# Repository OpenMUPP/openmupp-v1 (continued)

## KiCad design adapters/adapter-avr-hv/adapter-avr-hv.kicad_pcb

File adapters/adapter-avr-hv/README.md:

# adapter-avr-hv

This adapter programs AVR parts that need a high voltage (12 V) on one pin. This is necessary when a fuse disables the normal programming interface. Examples are the RSTDISBL fuse and the RSTPINCFG fuse. The adapter has slot 8 (R1 = 39 kΩ).

The probe supplies all levels on J1 pin 19: 0 V, `VTREF` and VPP. See [Pin 19 states](../../docs/hardware.md#pin-19-states). The circuit details are in [adapters/README.md](../README.md).

## Connectors

| Ref | Type | Interface | Target parts | 12 V goes to |
|-----|------|-----------|--------------|--------------|
| J1 | 2 × 10 socket | Probe J4 | — | — |
| J2 | DIP-8 socket | HVSP | ATtiny13, ATtiny25/45/85 | Pin 1 (RESET) |
| J3 | DIP-14 socket | HVSP | ATtiny24/44/84 | Pin 4 (RESET) |
| J4 | 2 × 3 header | TPI and UPDI | ATtiny4/5/9/10, tinyAVR 0, 1 and 2 series, AVR DD | Pin 5 (RESET). With JP1 closed, also pin 1 (UPDI). |
| J5 | 1 × 4 header | Debug UART | Any | — |
| JP1 | 2-pin jumper header | HV select for J4 | — | — |

HVSP is high-voltage serial programming. TPI is the Tiny Programming Interface. UPDI is the Unified Program and Debug Interface.

Connect only one target at a time. VPP goes to J2, J3 and J4 at the same time.

### J2 and J3: HVSP sockets

Put the part directly into the socket. The probe supplies `VCC` from `VTREF`.

| HVSP signal | J1 pin | J2 (DIP-8) | J3 (DIP-14) |
|-------------|--------|------------|-------------|
| RESET (12 V) | 19 | 1 (PB5) | 4 (PB3) |
| SCI (clock) | 6 | 2 (PB3) | 2 (PB0) |
| SDI (data in) | 10 | 5 (PB0) | 7 (PA6) |
| SII (instruction in) | 17 | 6 (PB1) | 8 (PA5) |
| SDO (data out) | 8 | 7 (PB2) | 9 (PA4) |
| `VCC` | 1 | 8 | 1 |
| GND | 3, 5, 7, 9, 20 | 4 | 14 |

HVSP entry needs three Prog_enable pins at 0 while `VCC` comes up. On J2, these pins are SDI, SII and SDO. The probe drives SDI and SII low, and R4 holds SDO low. On J3, these pins are PA0, PA1 and PA2 (pins 13, 12 and 11). R7, R6 and R5 hold them low. The pin data is from the ATtiny25/45/85 data sheet (table 20-13) and the ATtiny24A/44A/84A data sheet (table 19-13).

### J4: TPI and UPDI header

J4 uses the Microchip 6-pin layout for TPI and UPDI (Atmel-ICE user guide, tables 3-4 and 3-7).

| Pin | Function | Net | J1 pin |
|-----|----------|-----|--------|
| 1 | TPI data or UPDI | `UPDI_HV` | 12, through Q2 |
| 2 | `VTREF` | `VTREF` | 1 |
| 3 | TPI clock | `SCI_TPICLK` | 6 |
| 4 | — | Open | — |
| 5 | RESET | `RESET_VPP` | 19 |
| 6 | GND | GND | GND |

TPI data and UPDI use the same pin, J1 pin 12. The probe drives this pin open drain, with a 10 kΩ pull-up. The target pulls `UPDI_HV` high with its internal pull-up. See [UPDI on J4 pin 12](../README.md#updi-on-j4-pin-12).

### JP1: HV select

JP1 selects the J4 pin that gets 12 V. Set JP1 before you connect the target.

| JP1 | 12 V on | Use for |
|-----|---------|---------|
| Open | Pin 5 only | TPI (ATtiny4/5/9/10). UPDI parts with a separate RESET pin, for example AVR DD. |
| Closed | Pin 1 (through D1) and pin 5 | tinyAVR 0, 1 and 2 series. UPDI and RESET are on the same pin. |

**CAUTION:** Do not close JP1 for a TPI part or an AVR DD part. Pin 1 then gets 12 V, and this can damage the part.

- TPI needs 12 V on RESET only when the RSTDISBL fuse is programmed.
- The AVR DD setting is not verified against a part. Read the data sheet of the part before you use it.
- With JP1 closed, pin 5 also gets VPP. Some tinyAVR target boards connect pin 5 to the UPDI pin. Check the target board before you use it.
- The firmware can read the JP1 position before it sets VPP on. See [UPDI high-voltage pulse](../README.md#updi-high-voltage-pulse).

### J5: debug UART

| Pin | Signal | J1 pin |
|-----|--------|--------|
| 1 | GND | GND |
| 2 | RX (probe input) | 14 |
| 3 | TX (probe output) | 13 |
| 4 | `VTREF` | 1 |

All adapters have this header (see [Rules for all adapters](../README.md#rules-for-all-adapters)).

## Other parts

| Ref | Value | Function |
|-----|-------|----------|
| R1 | 39 kΩ | Adapter ID, slot 8 |
| D1 | BAT54A | With JP1 closed, connects `RESET_VPP` to `UPDI_HV` (J4 pin 1). It blocks while pin 19 is at 0 V. |
| Q2 | FDV301N | Pass switch between `UPDI_HV` and `UPDI`. It blocks 12 V from J1 pin 12. |
| R4 | 10 kΩ | Holds SDO (J2 pin 7) low at HVSP entry |
| R5, R6, R7 | 10 kΩ | Hold PA0, PA1 and PA2 on J3 low at HVSP entry |

J1 pins 2, 4, 11, 15 and 18 are not used.

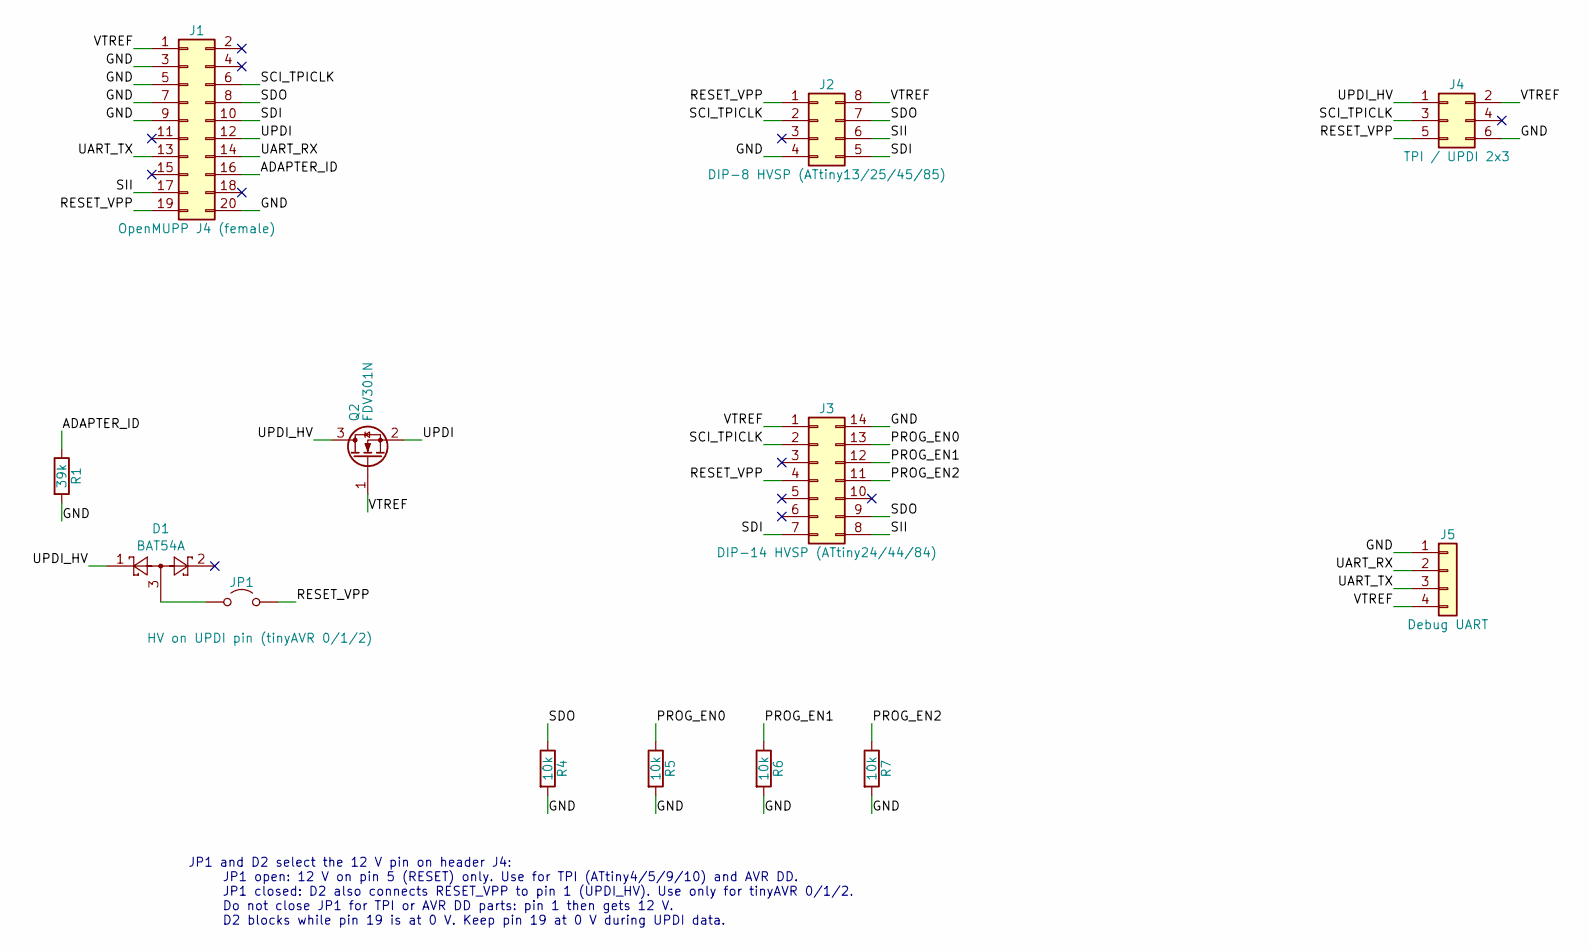
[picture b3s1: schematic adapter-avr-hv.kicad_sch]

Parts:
D1: BAT54A; SOT-23
J1: OpenMUPP J4 (female); PinSocket_2x10_P2.54mm_Horizontal
J2: DIP-8 HVSP (ATtiny13/25/45/85); DIP-8_W7.62mm_Socket
J3: DIP-14 HVSP (ATtiny24/44/84); DIP-14_W7.62mm_Socket
J4: TPI / UPDI 2x3; PinHeader_2x03_P2.54mm_Vertical
J5: Debug UART; PinHeader_1x04_P2.54mm_Vertical
JP1: HV on UPDI pin (tinyAVR 0/1/2); PinHeader_1x02_P2.54mm_Vertical
Q2: FDV301N; SOT-23
R1: 39k; R_0603
R4, R5, R6, R7: 10k; R_0603

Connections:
/ADAPTER_ID: J1.16, R1.1
/GND: J1.3, J1.5, J1.7, J1.9, J1.20, J2.4, J3.14, J4.6, J5.1, R1.2, R4.2, R5.2, R6.2, R7.2
/PROG_EN0: J3.13, R5.1
/PROG_EN1: J3.12, R6.1
/PROG_EN2: J3.11, R7.1
/RESET_VPP: J1.19, J2.1, J3.4, J4.5, JP1.2 (B)
/SCI_TPICLK: J1.6, J2.2, J3.2, J4.3
/SDI: J1.10, J2.5, J3.7
/SDO: J1.8, J2.7, J3.9, R4.1
/SII: J1.17, J2.6, J3.8
/UART_RX: J1.14, J5.2
/UART_TX: J1.13, J5.3
/UPDI: J1.12, Q2.2 (S)
/UPDI_HV: D1.1, J4.1, Q2.3 (D)
/VTREF: J1.1, J2.8, J3.1, J4.2, J5.4, Q2.1 (G)
unnamed: D1.3, JP1.1 (A)

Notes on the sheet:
JP1 and D2 select the 12 V pin on header J4: JP1 open: 12 V on pin 5 (RESET) only. Use for TPI (ATtiny4/5/9/10) and AVR DD. JP1 closed: D2 also connects RESET_VPP to pin 1 (UPDI_HV). Use only for tinyAVR 0/1/2. Do not close JP1 for TPI or AVR DD parts: pin 1 then gets 12 V. D2 blocks while pin 19 i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

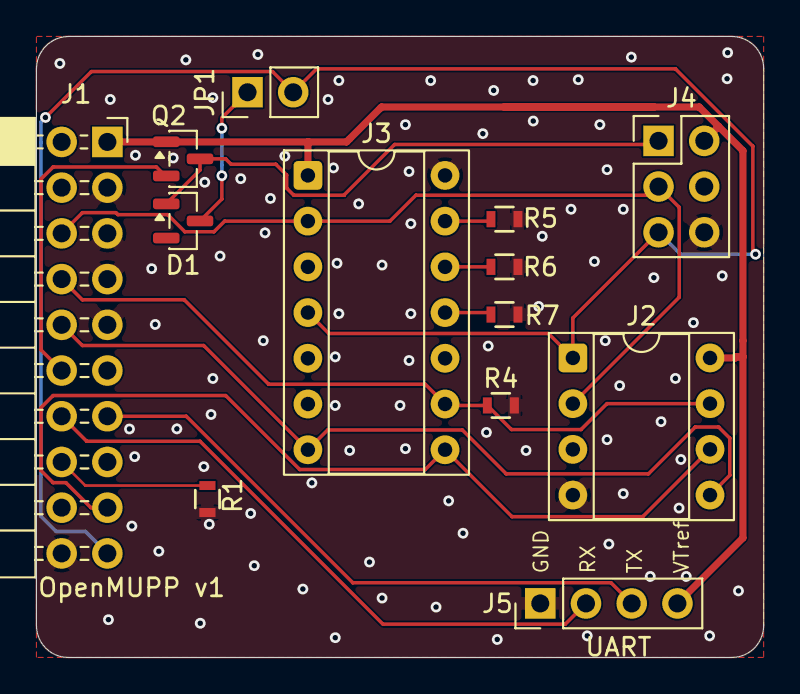
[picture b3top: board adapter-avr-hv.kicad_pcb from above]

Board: 2 copper layers, 40.4 x 34.5 mm, 13 parts (0 on the bottom side), 16 nets.

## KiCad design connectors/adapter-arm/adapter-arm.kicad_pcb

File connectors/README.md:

# Target adapters for OpenMUPP v1

Each folder is a KiCad 10 project with the schematic of one target adapter. The projects have no board layout yet.

| Folder                                     | Adapter          | Slot | R<sub>ID</sub> | Target connectors                                              |
|--------------------------------------------|------------------|------|----------------|----------------------------------------------------------------|
| [adapter-avr-jtag-isp](adapter-avr-jtag-isp/) | AVR variant A | 1 | 1.1 kΩ | Atmel-ICE 10 (1.27 mm), AVR JTAG 10 (2.54 mm), 2 × 3 ISP |
| [adapter-arm](adapter-arm/)                | Arm              | 4    | 6.8 kΩ         | ARM JTAG 20, Cortex Debug 10, STDC14                           |
| [adapter-pin-header](adapter-pin-header/)  | Pin header       | 5    | 10 kΩ          | 1 × 6 SWD / CH32 / SWIM, 1 × 4 ST SWIM, 2 × 5 WCH-LinkE layout |
| [adapter-avr-hv](adapter-avr-hv/)          | AVR high voltage | 8    | 39 kΩ          | DIP-8 and DIP-14 sockets (HVSP), 2 × 3 TPI and UPDI            |
| [adapter-pic-hv](adapter-pic-hv/)          | PIC high voltage | 9    | 91 kΩ          | PICkit ICSP 1 × 6                                              |

The slot table and the J4 pinout are in the [main README](../README.md#adapter-boards-and-adapter-id).

## Rules for all adapters

1. J1 is a female 2 × 10 header, 2.54 mm. It plugs directly onto J4 of the probe. The pin numbers of J1 are the J4 pin numbers.
2. One 1 % resistor (R1) goes from J1 pin 16 to GND. J1 pin 16 never goes to the target.
3. J1 pin 2 (reserved) stays open. J1 pin 19 (VPP) stays open on each adapter that is not a high-voltage adapter.
4. Each adapter has a 1 × 4 debug UART header: 1 GND, 2 RX (probe input), 3 TX (probe output), 4 `VTREF`. The labels are from the probe side. Pins 1 to 3 have the same order as J2 on the main board. Pin 4 lets the UART work without a debug connector to the target.
5. Connect only one target connector at a time.

## Female header on J4

J4 on the probe is a shrouded, right-angle header (`IDC-Header_2x10_P2.54mm_Horizontal`). The adapter schematics use `PinSocket_2x10_P2.54mm_Horizontal` for J1, so the adapter board is in the same plane as the probe. Before layout, check these items:

- **Fit.** The socket body must go into the shroud of J4. Measure the shroud opening and the socket body.
- **Pin mirror.** The socket and the header mate face to face. Make sure that J1 pin 1 touches J4 pin 1 in the layout.
- **Polarity.** A plain socket has no key, so it can go in rotated by 180°. Then J1 pin 16 touches a probe GND pin, and the probe pin 16 touches an adapter GND pin. The adapter ID reads 0 Ω (the fault slot). The firmware must then keep the shifter outputs, the target power and VPP off. Use a keyed socket, or add a mechanical key on the adapter board, if possible.

## RESET and MCLR on J4 pin 19

`adapter-avr-hv` and `adapter-pic-hv` connect the target RESET or MCLR pin directly to J1 pin 19. The nets are `RESET_VPP` and `MCLR_VPP`. The probe gives pin 19 three levels: 0 V (reset), `VTREF` (run) and VPP (program). See [Pin 19 states](../docs/hardware.md#pin-19-states). Thus the adapters have no reset circuit, and J1 pin 18 (`AUX2`) is not used.

HVSP entry needs RESET at 0 V while `VCC` comes up. Then RESET must go to 12 V after a short time. Q6 on the probe holds pin 19 at 0 V. The firmware can set `VPP_ON` before `VCC` comes up, because Q6 holds pin 19 low against the current limit. Then the firmware releases Q6 at the time that the data sheet gives. Pin 19 then goes to VPP in some µs.

## UPDI on J4 pin 12

UPDI uses J4 pin 12 (nRESET / debugWIRE), not J4 pin 4 (SWDIO). The reasons:

- The UPDI pin of a tinyAVR is a weak driver. The ATtiny1614/16/17 data sheet (DS40002204A, table 36-16, VOL2) guarantees only 0.1 mA at 1.8 V and 0.5 mA at 5 V.
- J4 pin 4 has a 2.2 kΩ pull-up on the probe. The target must then sink 0.8 mA to 2.3 mA. See issue [#6](https://github.com/OpenMUPP/openmupp-v1/issues/6).
- J4 pin 12 has a 10 kΩ pull-up. The target must sink 0.18 mA at 1.8 V and 0.5 mA at 5 V.
- J4 pin 12 is open-drain (Q1 on the probe). This is the physical layer that UPDI expects.

Effects on the firmware:

- The read-back of J4 pin 12 goes to PB11 (USART3_RX). The USART receives UPDI and sees its own transmit.
- The CH32V307 USART cannot invert TX, so the firmware sends UPDI in software through Q1 (PB12). debugWIRE uses the same method.
- The rise time with 10 kΩ and about 30 pF to 50 pF is about 0.3 µs to 0.5 µs. This is sufficient for 225 kbps (the maximum UPDI rate at 1.8 V). It is not sufficient for 0.9 Mbps. These values are estimates, not measurements.
- The debug UART (J4 pins 13 and 14) stays free during UPDI.

On `adapter-avr-hv`, TPI data also uses J4 pin 12, through the same path as UPDI. The TPIDATA pin of the ATtiny4/5/9/10 has an internal pull-up in TPI mode (20 kΩ to 50 kΩ). The target drives a 0 and the first 1 of a sequence. Then the pull-up holds the line high (ATtiny4/5/9/10 data sheet DS40002060A, section 15.3.8). Thus TPI and UPDI see the same physical layer: open drain with a pull-up. Other TPI adapters can still use J4 pin 4.

## UPDI high-voltage pulse

`adapter-avr-hv` has one 2 × 3 header (J4) for TPI and UPDI. JP1, a 2-pin jumper header, selects the pin that gets the high voltage (HV):

| JP1 | Use | Pin 1 (data) | Pin 5 | HV goes to |
|-----|-----|--------------|-------|------------|
| Open | TPI (ATtiny4/5/9/10). UPDI with a separate RESET pin, for example AVR DD. | `UPDI_HV` (through Q2 to J1 pin 12) | `RESET_VPP` (J1 pin 19) | Pin 5 |
| Closed | UPDI with HV on the UPDI pin (tinyAVR 0, 1 and 2 series) | `UPDI_HV` (through Q2 to J1 pin 12) | `RESET_VPP` (J1 pin 19) | Pin 1 and pin 5 |

On the tinyAVR 0, 1 and 2 series, the UPDI pin and the RESET pin are the same pin. The data sheet calls the HV entry "UPDI Enable with High-Voltage Override of RESET Pin". The HV detection level (V<sub>HVRST</sub>) is 11.5 V to 12.5 V. The AVR DD setting is not verified against a part. Check the data sheet of each part before you use it.

The TPIDATA pin and the AVR DD UPDI pin must not get 12 V. Thus JP1 must be open for these parts. With JP1 closed, pin 5 also gets VPP. On a tinyAVR target board, pin 5 is usually not connected, so this is permitted. Some target boards connect pin 5 to the UPDI pin. Then pin 19 at 0 V holds the UPDI line low. Check the target board before you use it.

The parts of the UPDI path:

1. D2 (BAT54W) and JP1 connect J1 pin 19 to `UPDI_HV` when JP1 is closed. D2 has a drop of about 0.3 V. Set VPP to about 12.3 V for 12 V on the UPDI pin. `RESET_VPP` has no diode, so it gets VPP directly.
2. Q2 (FDV301N) is a pass switch between `UPDI_HV` (drain) and `UPDI` (source, J1 pin 12). The gate is on `VTREF`. When `UPDI_HV` is at 12 V, Q2 is off and the 10 kΩ pull-up on the probe holds `UPDI` at `VTREF`. The body diode is then reverse biased. The ESD diode on J4 pin 12 of the probe clamps at about 6 V, so this protection is necessary.
3. While VPP is off, Q2 passes UPDI and TPI data in both directions. The probe pulls `UPDI` high (10 kΩ). The internal pull-up of the target pulls `UPDI_HV` high. The adapter has no pull-up on `UPDI_HV`, so it adds no load to the weak UPDI pad.
4. With JP1 closed, keep pin 19 at 0 V (`VPP_PD` high) during UPDI, except during the HV pulse. In the run state, pin 19 is at `VTREF`. Then R39 on the probe and D2 pull `UPDI_HV` up. When the target sends a 0, it must also sink this current: about 0.13 mA at 1.8 V and 0.45 mA at 5 V. The UPDI pad guarantees only 0.1 mA at 1.8 V. At 0 V on pin 19, D2 blocks and adds no load.
5. The firmware can read the JP1 position before it sets VPP on. Put pin 19 in the run state and set Q1 on. With JP1 closed, current flows from R39 through D2, Q2 and Q1. `VPP_SENSE2` then reads less than about 0.5 V. With JP1 open, `VPP_SENSE2` reads the run level. If the JP1 position does not agree with the selected target, the firmware must not set VPP on. This value is an estimate, not a measurement.

Limits:

- Q2 passes a low level only when `VTREF` is above V<sub>GS(th)</sub>. The FDV301N has 1.06 V maximum, so `VTREF` of 1.8 V is sufficient. The tinyAVR parts run from 1.8 V to 5.5 V.
- The gate-source voltage of the FDV301N must stay above −0.3 V. The source (`UPDI`) has a 10 kΩ pull-up to the gate potential (`VTREF`), so it does not go above the gate. Q2 leakage (I<sub>DSS</sub> 1 µA maximum at 20 V) moves `UPDI` by about 10 mV.
- A low-to-high edge on `UPDI_HV` above `VTREF` − V<sub>GS(th)</sub> comes from the target pull-up only. This is slower than on `UPDI`. Check the rise time at the UPDI baud rate and at the TPI clock rate.
- VPP goes to `RESET_VPP`. With JP1 closed, it also goes to `UPDI_HV` at the same time. Connect only one target to J2, J3 or J4.
- After the pulse, the line must return to the normal level quickly: the debugger drives it low 1 µs to 10 µs after the HV ends (data sheet figure 33-6). D2 cannot pull `UPDI_HV` down. The probe pulls J4 pin 12 low through its Q1. The adapter Q2 then conducts, because its gate is at `VTREF`, and pulls `UPDI_HV` low. At the same time, Q6 on the probe pulls pin 19 to 0 V in less than 1 µs, so D2 blocks at once.
- The TPS2553 on the probe has a soft start of some milliseconds. Check the pulse timing in the target data sheet.

## HVSP pull-downs

HVSP entry needs the three Prog_enable pins at 0 while `VCC` comes up. R4 to R7 (10 kΩ) hold them low on `adapter-avr-hv`. These resistors are not in the adapter plan. The pins come from the ATtiny datasheets:

| Part              | Prog_enable[0..2]           | Resistors                                          |
|-------------------|-----------------------------|----------------------------------------------------|
| ATtiny13/25/45/85 | SDI, SII, SDO (PB0 to PB2)  | The probe drives SDI and SII low. R4 holds SDO low |
| ATtiny24A/44A/84A | PA0, PA1, PA2 (pins 13, 12, 11) | R5, R6, R7                                     |

J4 pin 8 (SDO input) is an input only, so the probe cannot hold SDO low. The target drives SDO against R4 after entry.

## Items to check before layout

- **WCH-LinkE layout.** The positions of GND, 3V3 and 5V on the WCH-LinkE header come from the schematic text only. Check them on a real WCH-LinkE. Pin 8 (3V3) connects to `VTREF`. Pin 10 (5V) stays open.
- **ST SWIM order.** Check the order (VDD, SWIM, GND, NRST) against ST UM1075.
- **1.27 mm headers.** Cortex Debug 10 and STDC14 use plain 1.27 mm pin headers in the schematic. Use shrouded, keyed parts (Samtec FTSH-105 and FTSH-107, or equal). Put their footprints in the `kicad-footprints` repository.
- **Atmel-ICE 10.** J2 on `adapter-avr-jtag-isp` is a plain 1.27 mm pin header in the schematic. Use a shrouded, keyed part, as for Cortex Debug 10. J4 (AVR JTAG 10, 2.54 mm) uses a shrouded IDC header.
- **Footprint libraries.** All resistors are 0603 and use `resistors:R_0603` from the `kicad-footprints` repository, as on the main board.

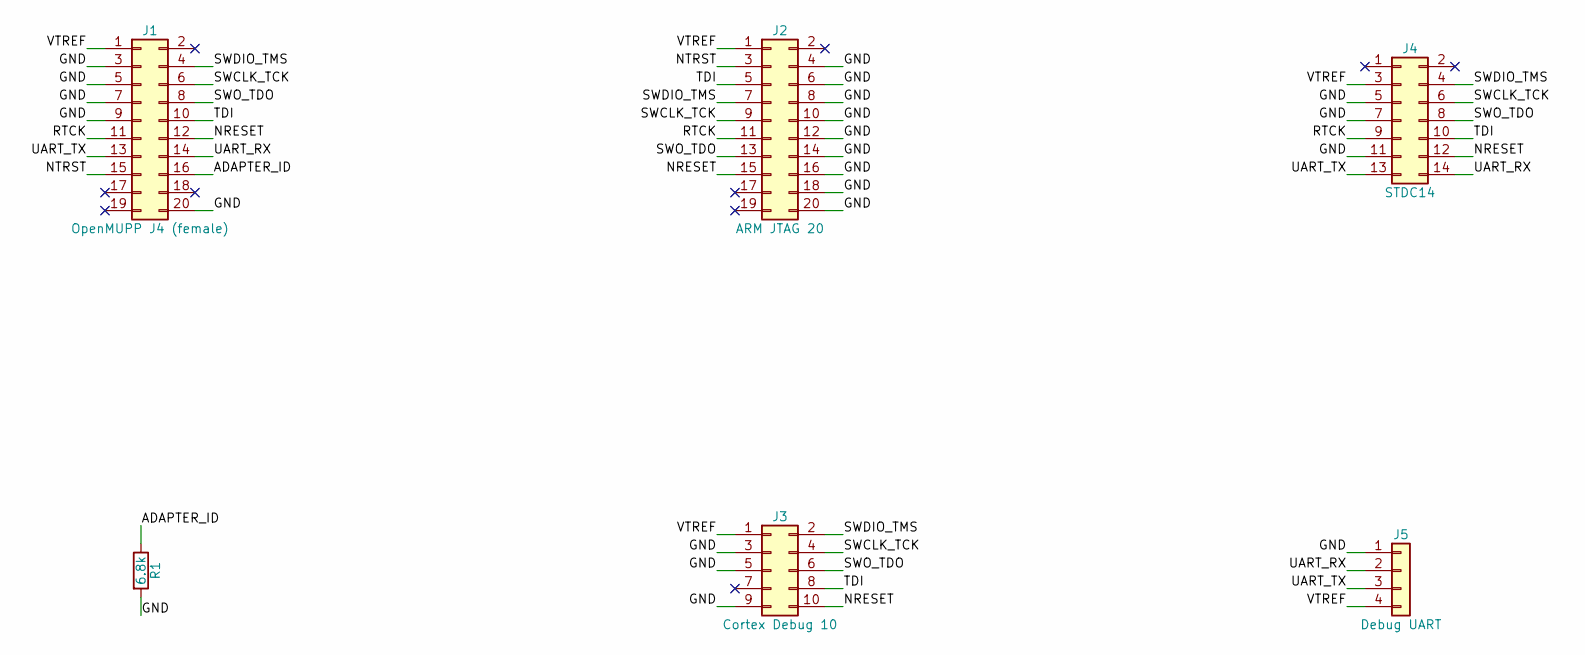
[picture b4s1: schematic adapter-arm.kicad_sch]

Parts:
J1: OpenMUPP J4 (female); PinSocket_2x10_P2.54mm_Horizontal
J2: ARM JTAG 20; IDC-Header_2x10_P2.54mm_Vertical
J3: Cortex Debug 10; PinHeader_2x05_P1.27mm_Vertical_SMD
J4: STDC14; PinHeader_2x07_P1.27mm_Vertical_SMD
J5: Debug UART; PinHeader_1x04_P2.54mm_Vertical
R1: 6.8k; R_0603

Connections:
/ADAPTER_ID: J1.16, R1.1
/GND: J1.3, J1.5, J1.7, J1.9, J1.20, J2.4, J2.6, J2.8, J2.10, J2.12, J2.14, J2.16, J2.18, J2.20, J3.3, J3.5, J3.9, J4.5, J4.7, J4.11, J5.1, R1.2
/NRESET: J1.12, J2.15, J3.10, J4.12
/NTRST: J1.15, J2.3
/RTCK: J1.11, J2.11, J4.9
/SWCLK_TCK: J1.6, J2.9, J3.4, J4.6
/SWDIO_TMS: J1.4, J2.7, J3.2, J4.4
/SWO_TDO: J1.8, J2.13, J3.6, J4.8
/TDI: J1.10, J2.5, J3.8, J4.10
/UART_RX: J1.14, J4.14, J5.2
/UART_TX: J1.13, J4.13, J5.3
/VTREF: J1.1, J2.1, J3.1, J4.3, J5.4

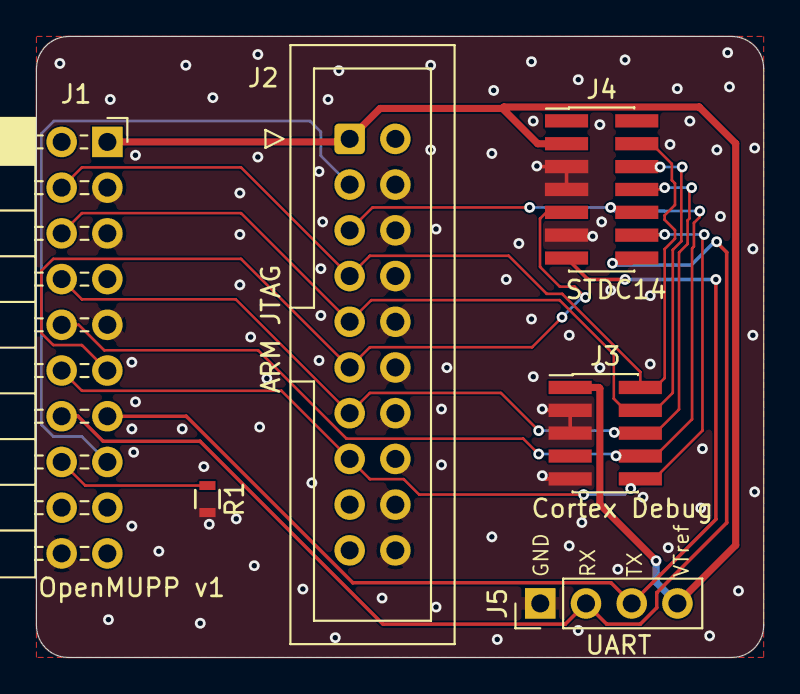
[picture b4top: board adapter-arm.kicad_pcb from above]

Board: 2 copper layers, 40.4 x 34.5 mm, 6 parts (0 on the bottom side), 12 nets.

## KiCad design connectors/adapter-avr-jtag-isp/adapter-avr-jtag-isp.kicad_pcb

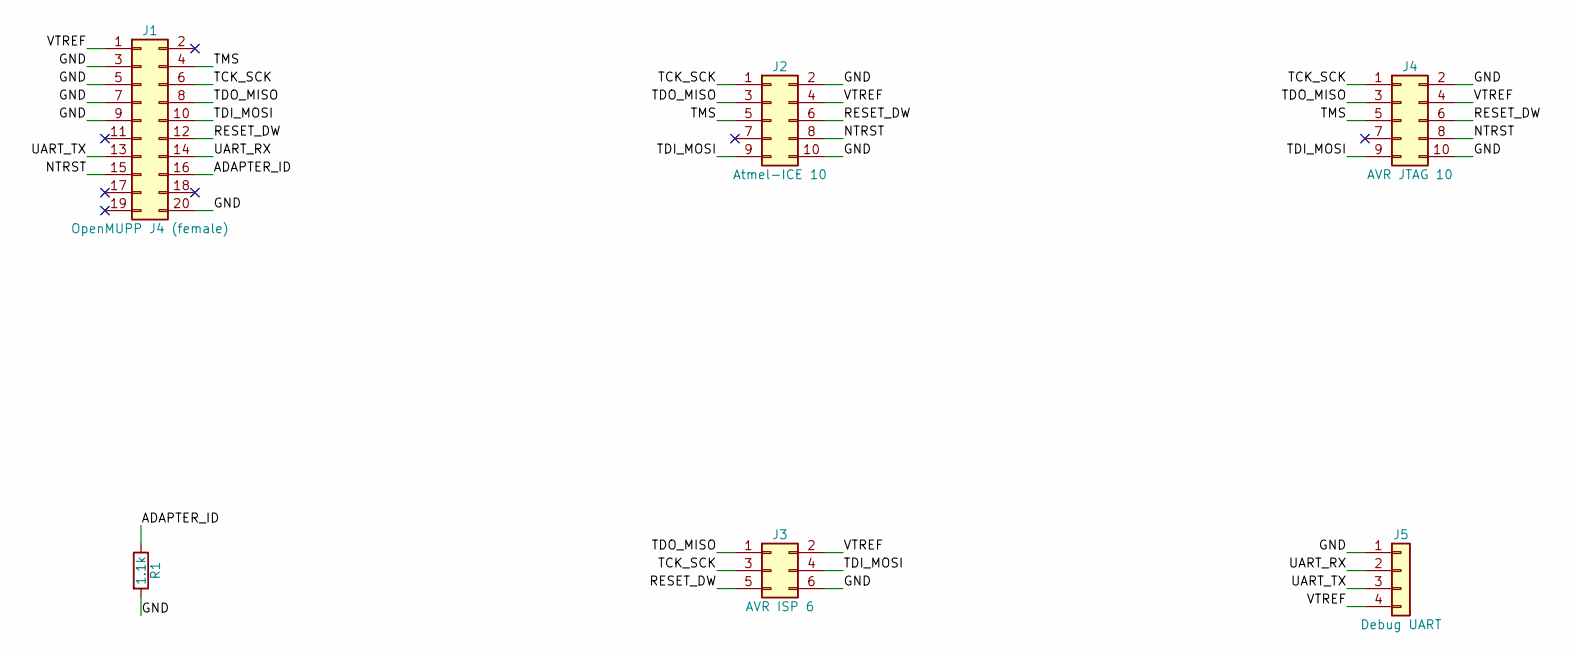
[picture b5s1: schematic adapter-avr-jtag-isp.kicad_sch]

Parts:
J1: OpenMUPP J4 (female); PinSocket_2x10_P2.54mm_Horizontal
J2: Atmel-ICE 10; PinHeader_2x05_P1.27mm_Vertical_SMD
J3: AVR ISP 6; PinHeader_2x03_P2.54mm_Vertical
J4: AVR JTAG 10; IDC-Header_2x05_P2.54mm_Vertical
J5: Debug UART; PinHeader_1x04_P2.54mm_Vertical
R1: 1.1k; R_0603

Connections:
/ADAPTER_ID: J1.16, R1.1
/GND: J1.3, J1.5, J1.7, J1.9, J1.20, J2.2, J2.10, J3.6, J4.2, J4.10, J5.1, R1.2
/NTRST: J1.15, J2.8, J4.8
/RESET_DW: J1.12, J2.6, J3.5, J4.6
/TCK_SCK: J1.6, J2.1, J3.3, J4.1
/TDI_MOSI: J1.10, J2.9, J3.4, J4.9
/TDO_MISO: J1.8, J2.3, J3.1, J4.3
/TMS: J1.4, J2.5, J4.5
/UART_RX: J1.14, J5.2
/UART_TX: J1.13, J5.3
/VTREF: J1.1, J2.4, J3.2, J4.4, J5.4

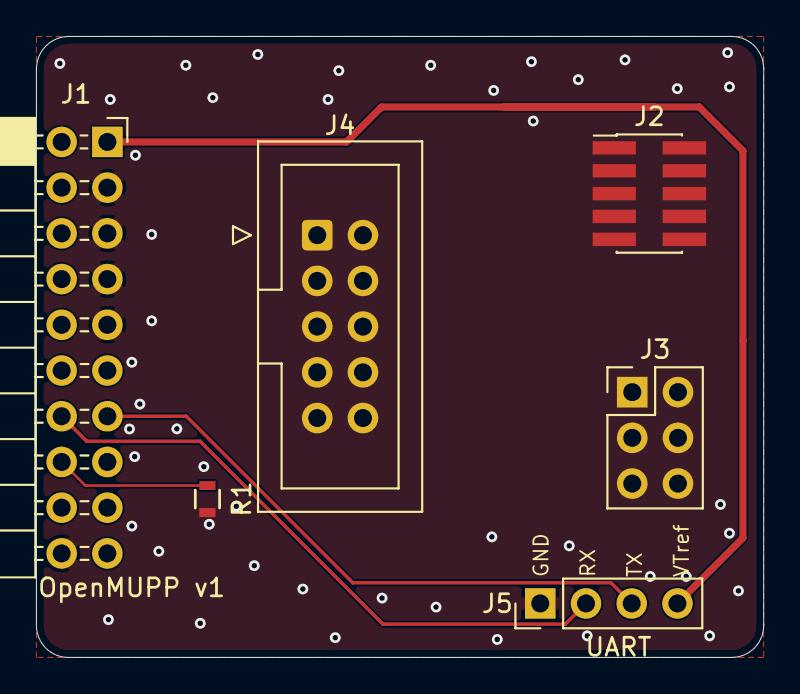
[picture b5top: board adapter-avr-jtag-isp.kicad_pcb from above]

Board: 2 copper layers, 40.4 x 34.5 mm, 6 parts (0 on the bottom side), 11 nets.

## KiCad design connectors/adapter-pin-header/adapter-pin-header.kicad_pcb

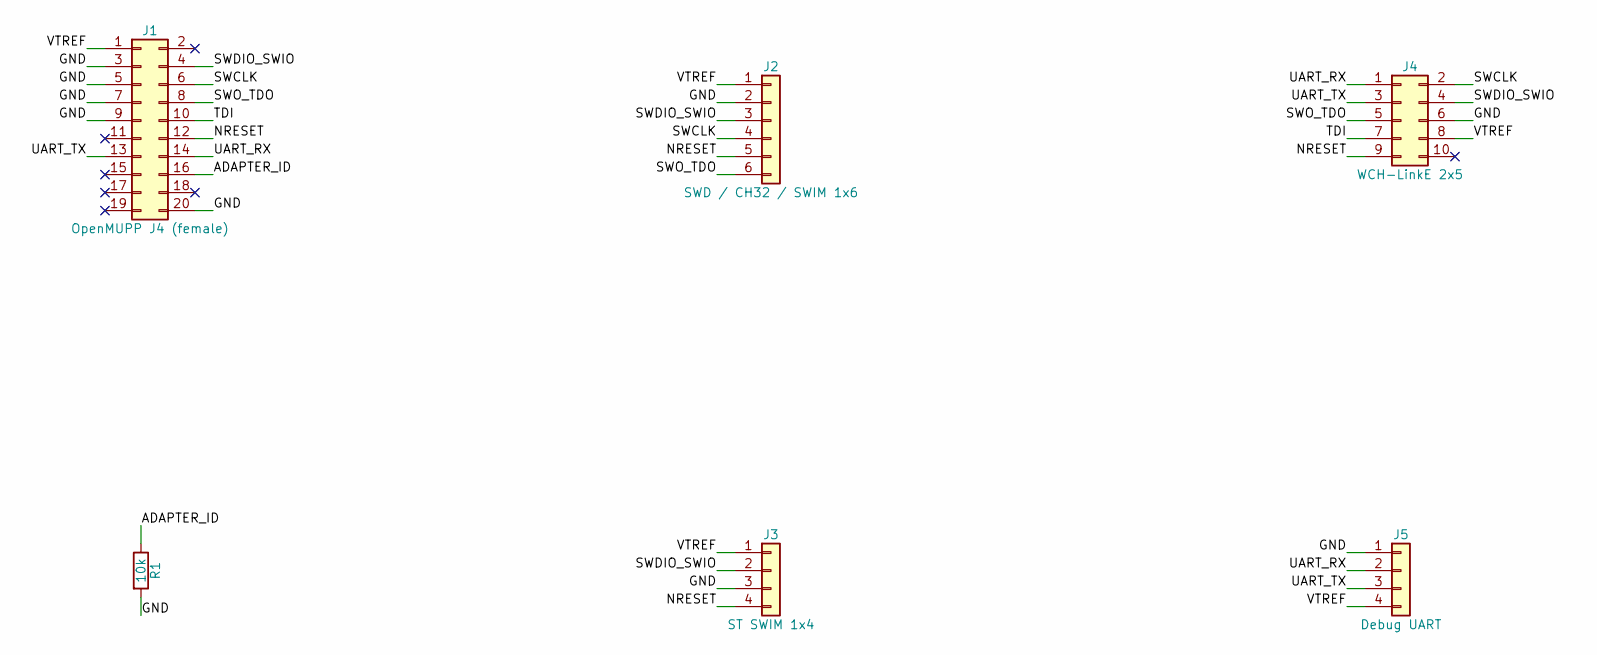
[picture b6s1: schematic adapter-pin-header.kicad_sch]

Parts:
J1: OpenMUPP J4 (female); PinSocket_2x10_P2.54mm_Horizontal
J2: SWD / CH32 / SWIM 1x6; PinHeader_1x06_P2.54mm_Vertical
J3: ST SWIM 1x4; PinHeader_1x04_P2.54mm_Vertical
J4: WCH-LinkE 2x5; PinHeader_2x05_P2.54mm_Vertical
J5: Debug UART; PinHeader_1x04_P2.54mm_Vertical
R1: 10k; R_0603

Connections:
/ADAPTER_ID: J1.16, R1.1
/GND: J1.3, J1.5, J1.7, J1.9, J1.20, J2.2, J3.3, J4.6, J5.1, R1.2
/NRESET: J1.12, J2.5, J3.4, J4.9
/SWCLK: J1.6, J2.4, J4.2
/SWDIO_SWIO: J1.4, J2.3, J3.2, J4.4
/SWO_TDO: J1.8, J2.6, J4.5
/TDI: J1.10, J4.7
/UART_RX: J1.14, J4.1, J5.2
/UART_TX: J1.13, J4.3, J5.3
/VTREF: J1.1, J2.1, J3.1, J4.8, J5.4

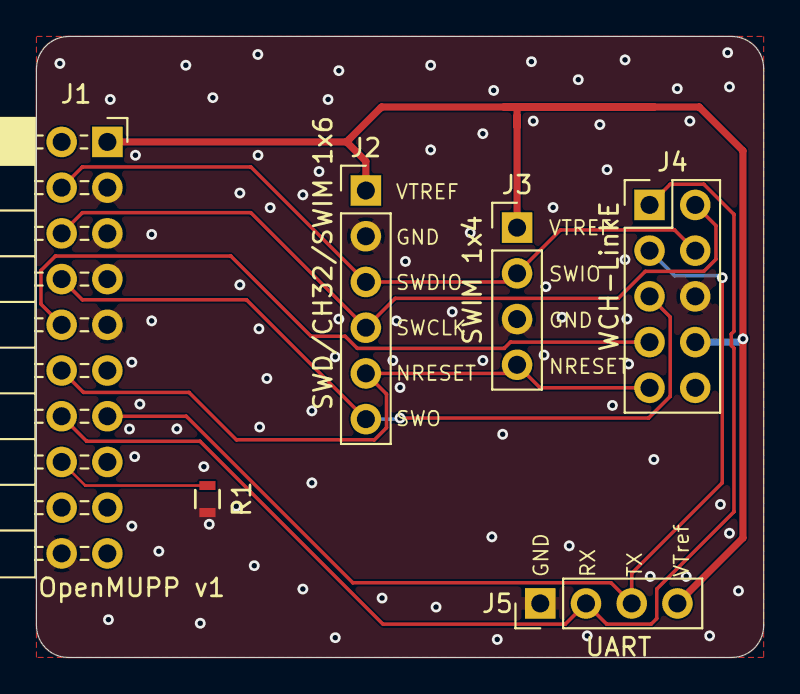
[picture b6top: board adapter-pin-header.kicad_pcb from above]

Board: 2 copper layers, 40.4 x 34.5 mm, 6 parts (0 on the bottom side), 10 nets.

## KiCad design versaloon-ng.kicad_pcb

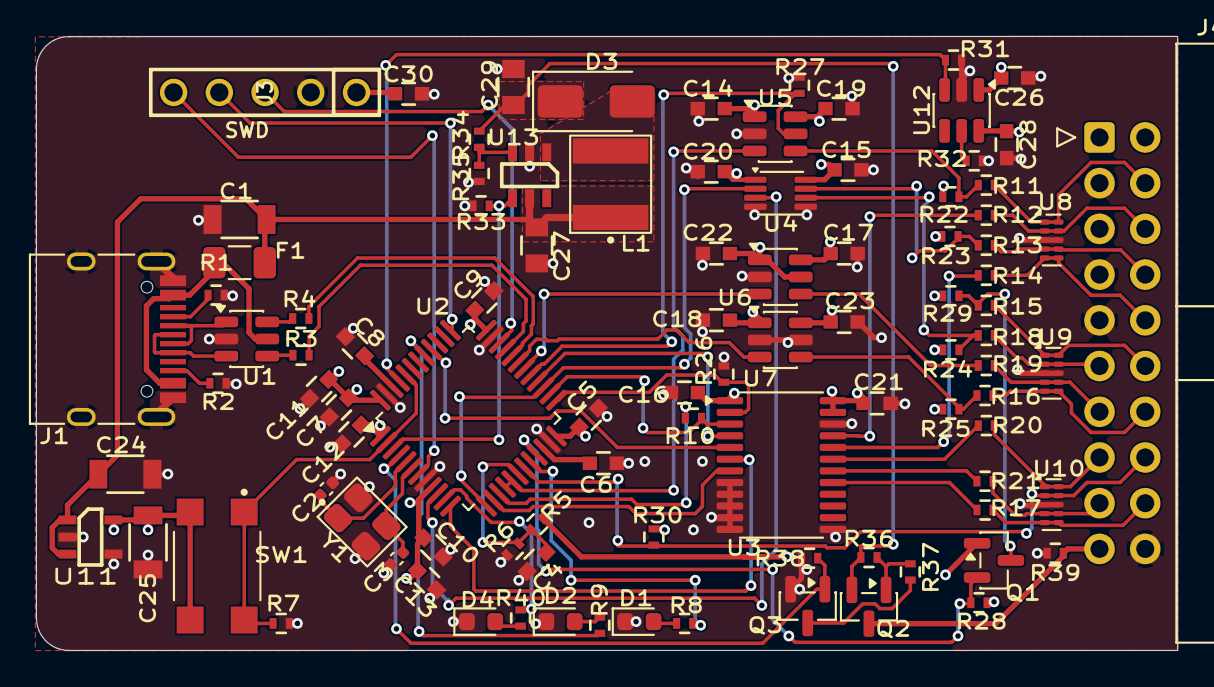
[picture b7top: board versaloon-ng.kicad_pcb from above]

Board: 4 copper layers, 63.4 x 34.1 mm, 97 parts (0 on the bottom side), 75 nets.

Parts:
C1, C24, C25: 10uF; C_1206
C2, C3: 5.6pF; C_0402_1005Metric
C4, C5, C7, C9, C10, C12, C14, C15, C16, C17, C18, C19, C20, C21, C22, C23, C30: 100nF; C_0603
C6, C8: 2.2uF; C_0603
C11: 4.7uF; C_0603
C13, C26, C28: 1uF; C_0603
C27, C29: 10uF; C_0805
D1, D4: LED state; LED_0603_1608Metric
D2: LED USB; LED_0603_1608Metric
D3: SL14; D_SMA
F1: 750mA; Fuse_1206_3216Metric
J1: USB_C_Receptacle_USB2.0_16P; USB_C_Receptacle_HRO_TYPE-C-31-M-12
J3: SWD; CON_HDR_1x5_2.54mm
J4: Target connector; IDC-Header_2x10_P2.54mm_Horizontal
L1: 22uH; L_FNR5040S
Q1, Q3: BSS138; SOT-23
Q2: AO3401A; SOT-23
R1, R2: 5K1; R_0402
R3, R4: 22R; R_0402
R5, R6, R26, R27, R31, R33, R36, R38, R39: 100k; R_0402
R7, R22, R23, R24, R25, R28, R29, R30, R35, R37: 10k; R_0402
R8, R9, R40: 1k; R_0402
R10: 0R; R_0402
R11, R12, R13, R14, R15, R16, R17, R18, R19, R20, R21: 33R; R_0402
R32: 51k; R_0402
R34: 191k; R_0402
SW1: BOOT0; SW_Push_HanElectricity_TS1109_4.5x4.5mm_H3.8mm
U1: USBLC6-2SC6; SOT-23-6
U2: STM32H523CCTx; LQFP-48_7x7mm_P0.5mm
U3: SN74LXC8T245; TSSOP-24_4.4x7.8mm_P0.65mm
U4: SN74LXC2T45; VSSOP-8_2.3x2mm_P0.5mm
U5, U6, U7: SN74LXC1T45; SOT-23-6
U8, U9, U10: TPD4E05U06DQA; USON-10_2.5x1.0mm_P0.5mm
U11: XC6220B331MR-G; SOT23_5L
U12: TPS2553; SOT-23-6
U13: MT3608; SOT23_6L
Y1: 24MHz; Crystal_SMD_NDK_NX3225GA_3.2x2.5mm

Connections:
+3.3V: C5.1, C7.1, C9.1, C10.1, C11.1, C12.1, C13.1, C14.1, C16.1, C18.1, C20.1, C22.1, C25.1, C26.1, C30.1, J3.1, Q1.1 (G), R28.1, R30.1, SW1.2, U2.1 (VBAT), U2.9 (VDDA), U2.24 (VDD), U2.36 (VDD), U2.48 (VDD), U3.1 (V_{CCA}), U4.1 (VCCA), U5.1 (VCCA), U6.1 (VCCA), U6.5 (DIR), U7.1 (VCCA), U11.5 (OUT), U12.1 (IN)
+5V: C1.1, C24.1, C27.1, F1.1, L1.1, U11.1 (IN), U11.3 (EN), U13.5 (IN)
/ADAPTER_ID: J4.16, R30.2, U2.19 (PB1), U10.2 (D1-), U10.9 (NC)
/AUX1: U2.12 (PA2), U3.6 (A4)
/AUX2: U2.14 (PA4), U3.7 (A5)
/BOOT0: R7.1, SW1.1, U2.2 (PC13), U2.44 (BOOT0)
/DIR_OUT: R26.1, U2.25 (PB12), U3.2 (DIR)
/DIR_SWDIO: R27.1, U2.29 (PA8), U5.5 (DIR)
/HSE_IN: C2.1, U2.5 (PH0), Y1.1
/HSE_OUT: C3.1, U2.6 (PH1), Y1.3
/LED_STATE1: R8.1, U2.20 (PB2)
/LED_STATE2: R40.1, U2.11 (PA1)
/LED_USB: R9.1, U2.41 (PB5)
/RTCK: U2.10 (PA0), U4.3 (A2)
/SRST: Q1.2 (S), R28.2, U2.21 (PB10)
/TARGET_PWR_EN: R31.1, U2.45 (PB8), U12.3 (EN)
/TCK: R10.2, U2.26 (PB13), U3.3 (A1)
/TDI: U2.28 (PB15), U3.4 (A2)
/TDO: U2.13 (PA3), U2.27 (PB14), U4.2 (A1)
/TMS_SWDIO: U2.16 (PA6), U2.17 (PA7), U5.3 (A)
/TRST: U2.40 (PB4(NJTRST)), U3.5 (A3)
/Target interface/xAUX1: J4.17, R21.1, U10.4 (D2+), U10.7 (NC)
/Target interface/xAUX2: J4.18, R17.1, U10.5 (D2-), U10.6 (NC)
/Target interface/xRST: J4.12, R15.1, U9.1 (D1+), U9.10 (NC)
/Target interface/xRTCK: J4.11, R18.1, U9.2 (D1-), U9.9 (NC)
/Target interface/xRX: J4.14, R16.1, U9.5 (D2-), U9.6 (NC)
/Target interface/xTCK: J4.6, R12.1, U8.2 (D1-), U8.9 (NC)
/Target interface/xTDI: J4.10, R14.1, U8.5 (D2-), U8.6 (NC)
/Target interface/xTDO: J4.8, R13.1, U8.4 (D2+), U8.7 (NC)
/Target interface/xTMS: J4.4, R11.1, U8.1 (D1+), U8.10 (NC)
/Target interface/xTRST: J4.15, R20.1, U10.1 (D1+), U10.10 (NC)
/Target interface/xTX: J4.13, R19.1, U9.4 (D2+), U9.7 (NC)
/UART_RX: U2.31 (PA10), U7.3 (A)
/UART_TX: U2.30 (PA9), U6.3 (A)
/VPP_EN: R33.1, U2.3 (PC14), U13.4 (EN)
/VPP_ON: Q3.1 (G), R38.1, U2.4 (PC15)
/VTREF_SENSE: C4.1, R5.2, R6.1, U2.18 (PB0)
GND: C1.2, C2.2, C3.2, C4.2, C5.2, C6.2, C7.2, C8.2, C9.2, C10.2, C11.2, C12.2, C13.2, C14.2, C15.2, C16.2, C17.2, C18.2, C19.2, C20.2, C21.2, C22.2, C23.2, C24.2, C25.2, C26.2, C27.2, C28.2, C29.2, C30.2, D1.1 (K), D2.1 (K), D4.1 (K), J1.A1 (GND), J1.A12 (GND), J1.B1 (GND), J1.B12 (GND), J1.S1 (SHIELD), J3.2, J4.3, J4.5, J4.7, J4.9, J4.20, Q3.2 (S), R1.2, R2.1, R6.2, R7.2, R26.2, R27.2, R31.2, R32.2, R33.2, R35.2, R38.2, R39.2, U1.2 (GND), U2.8 (VSSA), U2.23 (VSS), U2.35 (VSS), U2.47 (VSS), U3.8 (A6), U3.9 (A7), U3.10 (A8), U3.11 (GND), U3.12 (GND), U3.13 (GND), U3.22 (~OE), U4.4 (GND), U4.5 (DIR), U5.2 (GND), U6.2 (GND), U7.2 (GND), U7.5 (DIR), U8.3 (GND), U8.8 (GND), U9.3 (GND), U9.8 (GND), U10.3 (GND), U10.8 (GND), U11.2 (GND), U11.4 (GND), U12.2 (GND), U13.2 (GND), Y1.2 (G), Y1.4 (G)
unnamed: C6.1, U2.22 (VCAP)
unnamed: C8.1, U2.46 (VCAP)
unnamed: D1.2 (A), R8.2
unnamed: D2.2 (A), R9.2
unnamed: D3.2 (A), L1.2, U13.1 (SW)
unnamed: C29.1, D3.1 (K), Q2.2 (S), R34.1, R36.1
unnamed: D4.2 (A), R40.2
unnamed: J1.A5 (CC1), R1.1
unnamed: J1.B5 (CC2), R2.2
unnamed: J1.A6 (D+), J1.B6 (D+), U1.3 (I/O2)
unnamed: J1.A7 (D-), J1.B7 (D-), U1.1 (I/O1)
unnamed: Q2.1 (G), R36.2, R37.1
unnamed: Q3.3 (D), R37.2
unnamed: R3.1, U1.4 (I/O2)
unnamed: R4.1, U1.6 (I/O1)
unnamed: R10.1, U2.15 (PA5)
unnamed: R32.1, U12.5 (ILIM)
unnamed: R34.2, R35.1, U13.3 (FB)
RESET: J3.5, U2.7 (NRST)
SWDCLK: J3.4, U2.37 (PA14(JTCK)
SWDIO: J3.3, U2.34 (PA13(JTMS)
T_AUX1: R21.2, U3.18 (B4)
T_AUX2: R17.2, U3.17 (B5)
T_NRST: Q1.3 (D), R15.2, R29.2
T_RTCK: R18.2, R24.2, U4.6 (B2)
T_TCK: R12.2, U3.21 (B1)
T_TDI: R14.2, U3.20 (B2)
T_TDO: R13.2, R23.2, U4.7 (B1)
T_TMS_SWDIO: R11.2, R22.2, U5.4 (B)
T_TRST: R20.2, U3.19 (B3)
T_UART_RX: R16.2, R25.2, U7.4 (B)
T_UART_TX: R19.2, U6.4 (B)
USB_D+: R3.2, U2.33 (PA12)
USB_D-: R4.2, U2.32 (PA11)
VBUS: F1.2, J1.A4 (VBUS), J1.A9 (VBUS), J1.B4 (VBUS), J1.B9 (VBUS), U1.5 (VBUS)
VPP: J4.19, Q2.3 (D), R39.1
VTREF: C15.1, C17.1, C19.1, C21.1, C23.1, C28.1, J4.1, R5.1, R22.1, R23.1, R24.1, R25.1, R29.1, U3.23 (V_{CCB}), U3.24 (V_{CCB}), U4.8 (VCCB), U5.6 (VCCB), U6.6 (VCCB), U7.6 (VCCB), U12.6 (OUT)
